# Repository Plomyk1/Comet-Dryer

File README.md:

# Comet Dryer

Comet Dryer is a 3D printer filament dryer, with support for drying 2 spools at once!

I made this project, because I felt like trying to make something more complicated than all my previous projects. Decided on a filament dryer, since it was something I wanted to have, and the dryers i could buy seemed quite expensive for essentially just heating air inside a box

## Features:
- 50w Heater
- Fan for even distrubution of hot air
- A colorful 320x170 display
- Rotary encoder for navigating the menus
- UI fully written in C++ with the Adafruit GFX Library
- 13 Color themes
- 15 presets for drying different materials and dessicant

## CAD Model: 

The PCB and enclosure is put together with 5 M3x10 screws and heatset insters. Both the barrel jack and power switch is press fit into the enclosure. The heater and fan addembly is mounted with 2 M5x80 screws. The fan is screwed the the 3D printed bracket with 4 M4x20 screws

You can find all the STL and STEP files in the [CAD directory](/CAD)

## PCB:

The PCB has been designed to be manufactured by PCBWay. It may also fit the requirements of other manufacturers, but that is currently untested!
You can view the PCB wiring on KiCanvas with the button at the top of the readme

Diagram showing how the PCB is connected to power to the power supply

### If you want to make this dryer yourself, have a look at the assembly instructions in the [assembly.md](assembly.md) file!

## Credits:
Libraries I used: 
- [Adafruit ST7789](https://github.com/adafruit/Adafruit-ST7735-Library) by Adafruit Industries
- [Adafruit GFX](https://github.com/adafruit/Adafruit-GFX-Library) by Adafruit Industries
- [Adafruit AHTX0](https://github.com/adafruit/Adafruit_AHTX0) by Adafruit Industries
- [RotaryEncoder](https://github.com/mathertel/RotaryEncoder) by Matthias Hertel

AI use:

I have only used AI for debugging, and minor got help with electrical issues. All code in firmware.cpp was written by me

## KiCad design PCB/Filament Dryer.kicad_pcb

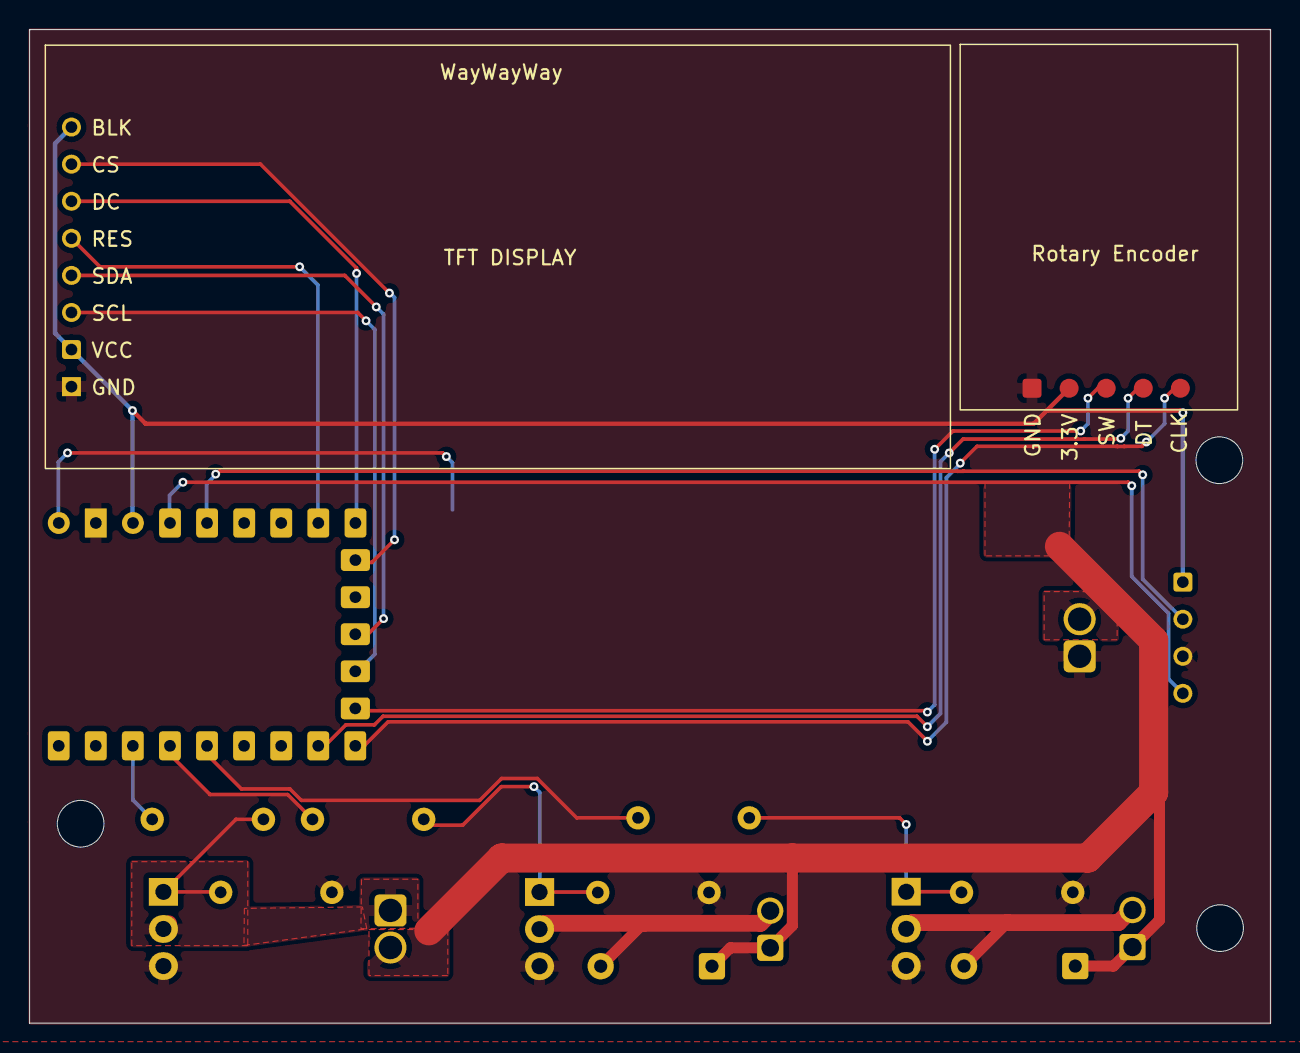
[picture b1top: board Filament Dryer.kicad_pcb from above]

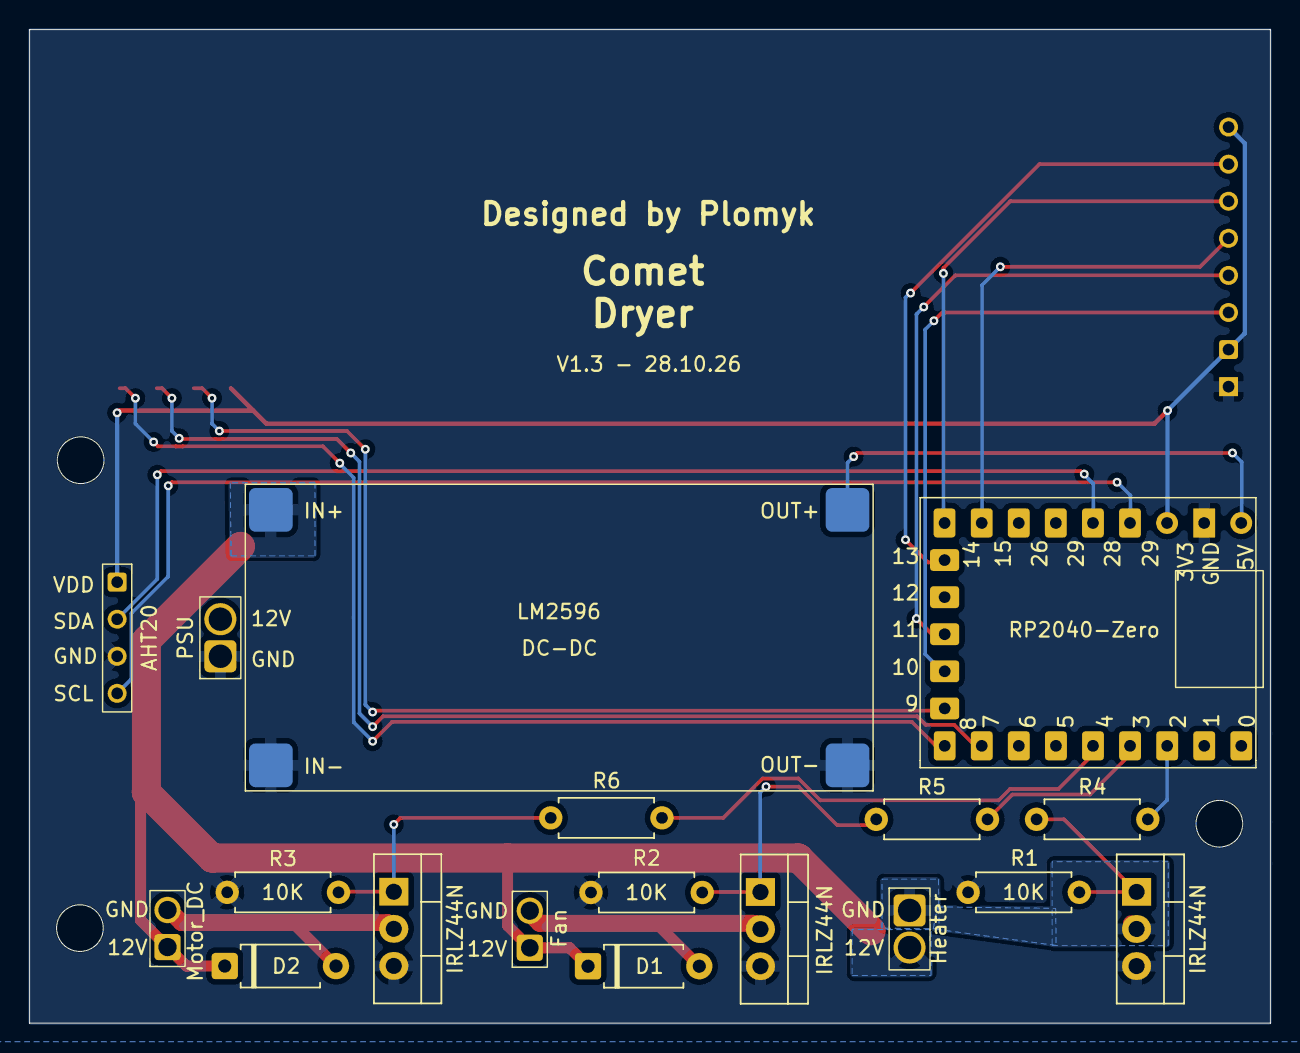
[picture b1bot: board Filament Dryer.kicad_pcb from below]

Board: 2 copper layers, 85.0 x 68.1 mm, 20 parts (17 on the bottom side), 23 nets.

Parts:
D1, D2: D; D_A-405_P7.62mm_Horizontal
M1: Fan; Fan footprint
M2: Motor_DC; Motor footprint
Q1, Q2, Q3: IRLZ44N; TO-220-3_Vertical
R1, R2, R3: 10K; R_Axial_DIN0207_L6.3mm_D2.5mm_P7.62mm_Horizontal
R4, R5, R6: 220; R_Axial_DIN0207_L6.3mm_D2.5mm_P7.62mm_Horizontal
U1: LM2596; LM2596 module footprint
U2: RP2040-Zero; RP2040-Zero Devboard footprint
U3: KY040; KY-040 Rotary encoder footprint
U4: 320x170 TFT; 1.9' TFT Display footprint
U5: Heater; Heater footprint
U6: PSU; PSU +12V footprint
U8: AHT20; Temperature sensor footprint

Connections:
+3.3V: U2.30 (3.3V), U3.2 (VCC), U4.2 (VCC), U4.8 (BLK), U8.1 (VDD)
+5V: U1.3 (OUT+), U2.32 (5V)
+12V: D1.1 (K), D2.1 (K), M1.1 (+), M2.1 (+), U1.1 (IN+), U5.2 (+12V), U6.2 (12V)
GND: Q1.3 (S), Q2.3 (S), Q3.3 (S), R1.2, R2.2, R3.2, U1.2 (IN-), U1.4 (OUT-), U2.31 (GND), U3.1 (GND), U4.1 (GND), U6.1 (GND), U8.3 (GND)
unnamed: D1.2 (A), M1.2 (-), Q2.2 (D)
unnamed: D2.2 (A), M2.2 (-), Q3.2 (D)
unnamed: Q1.2 (D), U5.1 (GND)
unnamed: Q1.1 (G), R1.1, R4.2
unnamed: Q2.1 (G), R2.1, R5.2
unnamed: Q3.1 (G), R3.1, R6.2
unnamed: R4.1, U2.2 (GPIO)
unnamed: R5.1, U2.3 (GPIO)
unnamed: R6.1, U2.4 (GPIO)
unnamed: U2.8 (GPIO), U3.5 (CLK)
unnamed: U2.7 (GPIO), U3.4 (DT)
unnamed: U2.9 (GPIO), U3.3 (SW)
unnamed: U2.13 (GPIO), U4.7 (CS)
unnamed: U2.14 (GPIO), U4.6 (DC)
unnamed: U2.15 (GPIO), U4.5 (RES)
unnamed: U2.10 (GPIO), U4.3 (SCL)
unnamed: U2.11 (GPIO), U4.4 (SDA)
unnamed: U2.29 (GPIO), U8.4 (SCL)
unnamed: U2.28 (GPIO), U8.2 (SDA)

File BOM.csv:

Item name,Qty,Total price (USD),Link,Notes
12v 10.5A PSU,1,"18,84",https://allegro.pl/produkt/zasilacz-modulowy-mean-well-12v-1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,I recommend getting this over a brick (barrel jack) power supply. Model: Mean Well LRS-150-12
PCB,1,"14,20",PCBWay,"Price quoted from PCBWay, since that is where I had my PCB manufactured. Includes Fees, shipping and taxes"
Container, 1, "7,35", https://www.ikea.com/pl/pl/p/ikea-365-pojemnik-na-zywnosc-z-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,
50mm Fan,1,"2,54",https://pl.aliexpress.com/item/1005006020005975.html,
AHT20 + BMP280 module,1,"2,18",https://pl.aliexpress.com/item/1005008239843130.html,Themperature and humidity sensor. The BMP280 isn't used
12v 50w PTC Heater,1,"5,77",https://pl.aliexpress.com/item/1005009279284775.html,
Female barrel jacks,1/10,"2,32",https://pl.aliexpress.com/item/1005012242149457.html,Only one of the 10 is used
"1.9"" TF 320x170 Display",1,"5,24",https://pl.aliexpress.com/item/1005010094030749.html,
KY040 Rotary encoder,1,"2,54",https://pl.aliexpress.com/item/1005008796691020.html,
IRLZ44N Mosfets,2/10,"3,36",https://pl.aliexpress.com/item/1005009630861300.html,2 of the 10 are used
KCD101-1 Power switch,1/5,"1,95",https://pl.aliexpress.com/item/1005013414323454.html,1/5 is used. Different listing from my order
RP2040-Zero,1,"4,99",https://www.waveshare.com/rp2040-zero.htm?sku=20335,
Step-down buck converter,1,"0,89",https://pl.aliexpress.com/item/1005012741976007.html,"LM2596S. 1,19USD shipping"
1N4007 Diode,1/10,"1,39",https://pl.aliexpress.com/item/1005012179615414.html,1/10 is used
Heatset inserts,5/50,"2,54",https://pl.aliexpress.com/item/1005006472702418.html,5/10 are used. M3xL4xOD4.5 50Pcs option
M3x10 screws,5/30,"1,57",https://www.leroymerlin.pl/produkty/sruba-walcowa-z-rowkiem-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,Local vendor. 5/30 screws screws in the package are used
M4x20 screws,2/20,"1,49",https://www.leroymerlin.pl/produkty/sruba-plaska-srednica-20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,Local vendor. 5/30 screws screws in the package are used
M5x80 screws,2/6,"1,57",https://www.leroymerlin.pl/produkty/sruba-plaska-srednica-6-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,Local vendor. 2/6 screws screws in the package are used
~1.5mm² Wire (16AWG),~0.5m,"1,00",https://www.leroymerlin.pl/produkty/przewod-elektryczny-ydyp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,I used some wires I already had. The lenght and price is estimated
Sunlu PETG HS,39.17g,"0,49",3D printed,Does not include previous designs / failed attempts
Professional LAB ASA,21.14g,"0,21",3D printed,Does not include previous designs / failed attempts
